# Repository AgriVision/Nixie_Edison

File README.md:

# Nixie_Edison
Circuit Diagram and PCB fur up cycled Nixie Display
For information: https://www.element14.com/community/community/design-challenges/upcycleit/blog/2017/03/22/upcycle-it-with-edison-upcycled-nixie-display-1-introduction

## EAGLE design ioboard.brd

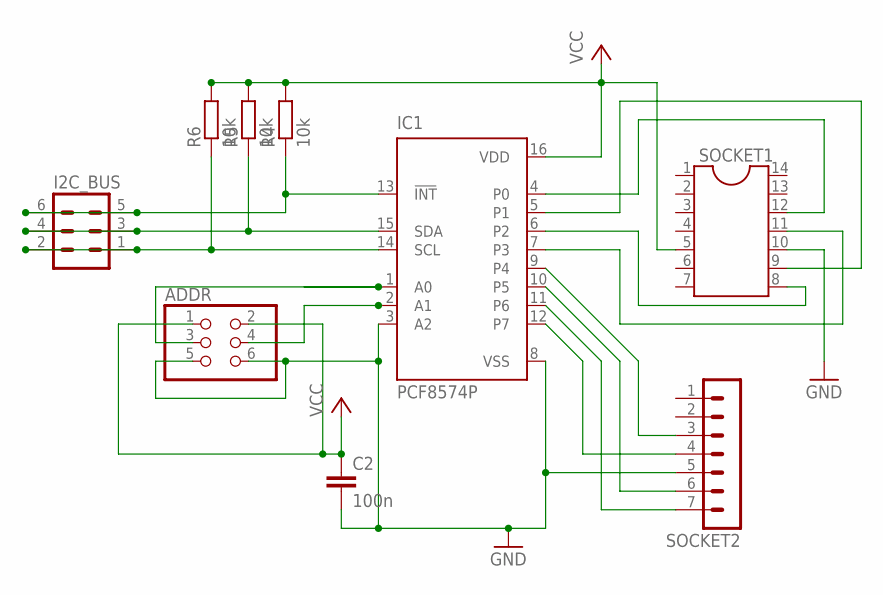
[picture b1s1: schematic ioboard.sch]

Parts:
ADDR: PINHD-2X3; 2X03
C2: 100n; C050-024X044
I2C_BUS: MA03-2
IC1: PCF8574P; DIL16
R4, R5, R6: 10k; 0207/10
SOCKET1: DIL14S; SOCKET-14
SOCKET2: MA07-1

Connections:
GND: ADDR.5, ADDR.6, C2.2, IC1.3 (A2), IC1.8 (VSS), SOCKET1.10, SOCKET2.5
unnamed: IC1.4 (P0), SOCKET1.12
unnamed: IC1.5 (P1), SOCKET1.9
unnamed: IC1.6 (P2), SOCKET1.8
unnamed: IC1.7 (P3), SOCKET1.11
unnamed: IC1.9 (P4), SOCKET2.3
unnamed: IC1.10 (P5), SOCKET2.6
unnamed: IC1.11 (P6), SOCKET2.7
unnamed: IC1.12 (P7), SOCKET2.4
unnamed: I2C_BUS.5, I2C_BUS.6, IC1.13 (!INT), R4.1
unnamed: I2C_BUS.1, I2C_BUS.2, IC1.14 (SCL), R6.1
unnamed: ADDR.3, IC1.1 (A0)
unnamed: ADDR.4, IC1.2 (A1)
unnamed: I2C_BUS.3, I2C_BUS.4, IC1.15 (SDA), R5.1
VCC: ADDR.1, ADDR.2, C2.1, IC1.16 (VDD), R4.2, R5.2, R6.2, SOCKET1.5

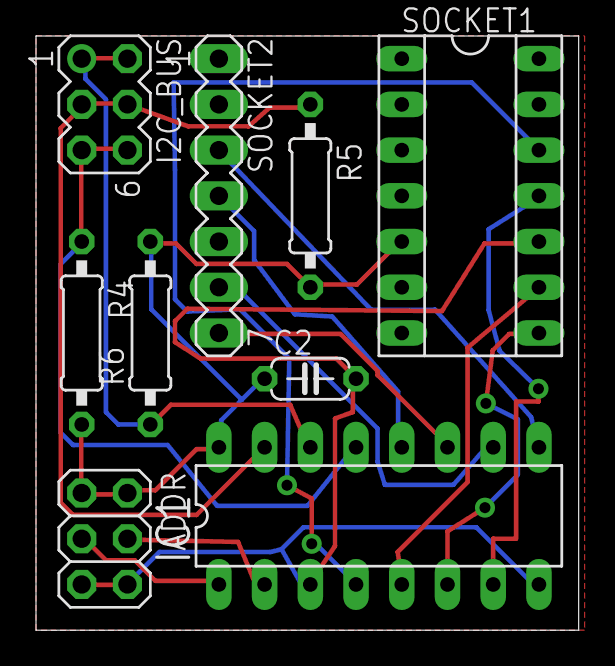
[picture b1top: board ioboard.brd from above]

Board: 2 copper layers, 30.1 x 33.0 mm, 9 parts (0 on the bottom side), 15 nets.

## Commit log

2017-04-12 initial git commit
